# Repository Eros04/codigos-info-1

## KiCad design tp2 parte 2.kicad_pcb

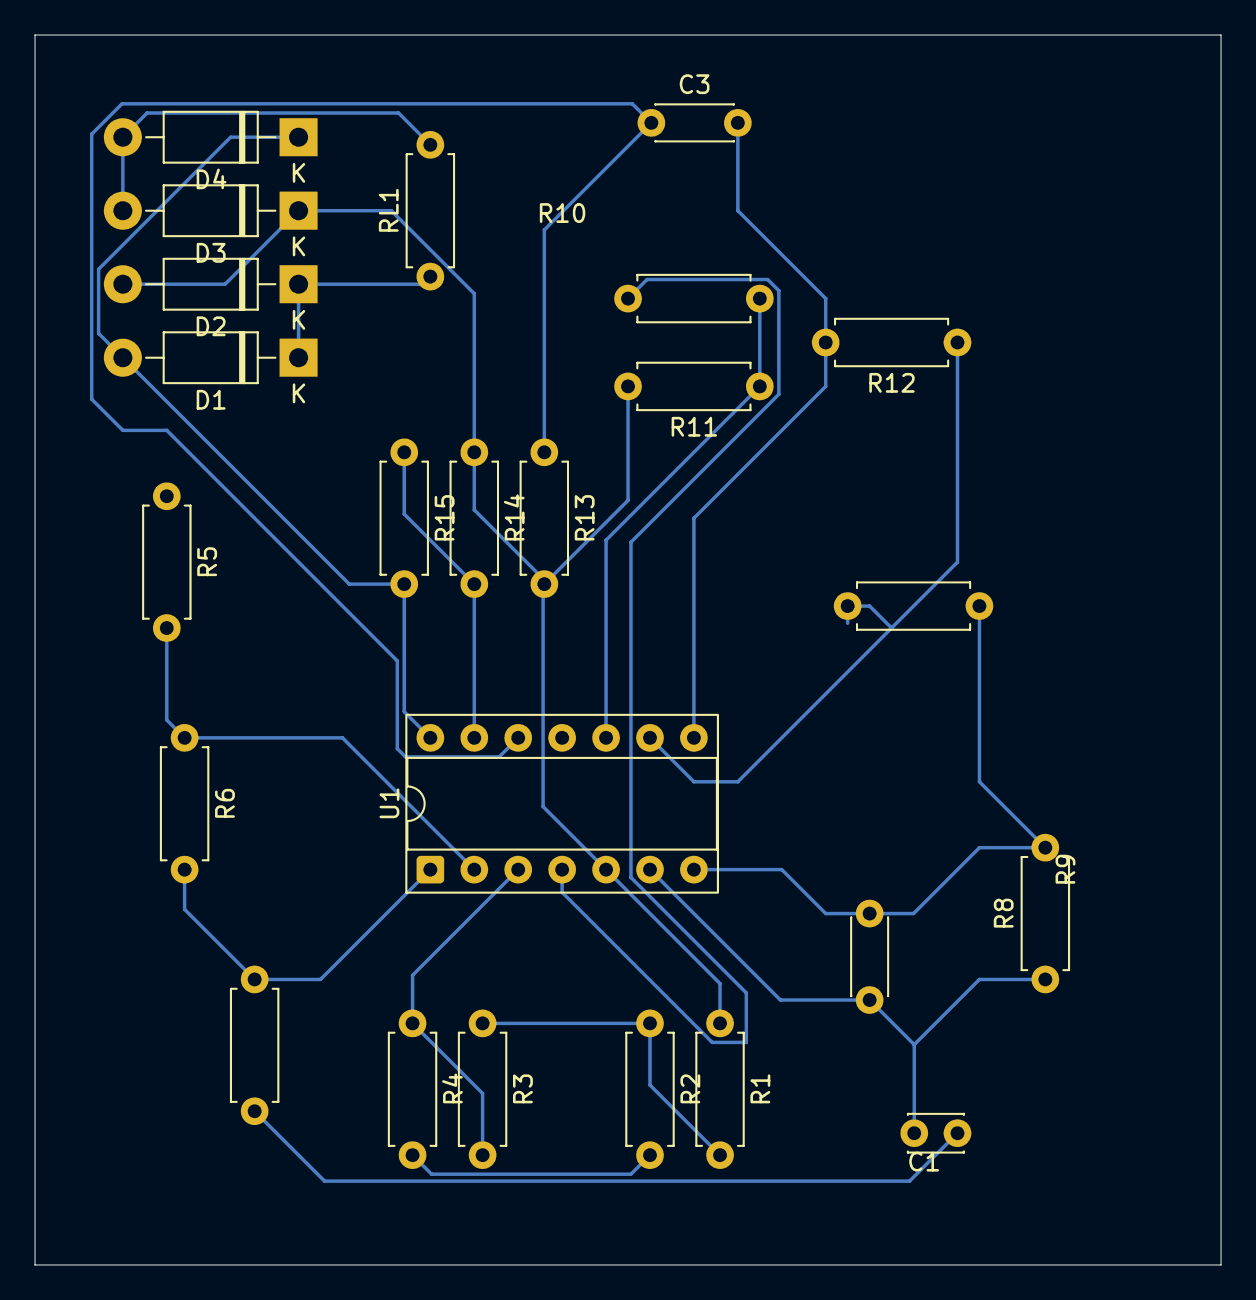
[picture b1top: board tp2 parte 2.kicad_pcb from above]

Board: 2 copper layers, 68.6 x 71.1 mm, 24 parts (0 on the bottom side), 18 nets.

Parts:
C1: 1n; C_Disc_D3.0mm_W2.0mm_P2.50mm
C2: 56p; C_Disc_D4.3mm_W1.9mm_P5.00mm
C3: 10n; C_Disc_D4.3mm_W1.9mm_P5.00mm
D1, D2, D3, D4: 1N5819; D_DO-41_SOD81_P10.16mm_Horizontal
R1: 450; R_Axial_DIN0207_L6.3mm_D2.5mm_P7.62mm_Horizontal
R2: 500; R_Axial_DIN0207_L6.3mm_D2.5mm_P7.62mm_Horizontal
R3, R4, R5, R6: 100k; R_Axial_DIN0207_L6.3mm_D2.5mm_P7.62mm_Horizontal
R7: 4k7; R_Axial_DIN0207_L6.3mm_D2.5mm_P7.62mm_Horizontal
R8: 63k; R_Axial_DIN0207_L6.3mm_D2.5mm_P7.62mm_Horizontal
R9: 56k; R_Axial_DIN0207_L6.3mm_D2.5mm_P7.62mm_Horizontal
R10, R14: 10k; R_Axial_DIN0207_L6.3mm_D2.5mm_P7.62mm_Horizontal
R11: 900; R_Axial_DIN0207_L6.3mm_D2.5mm_P7.62mm_Horizontal
R12: 28k; R_Axial_DIN0207_L6.3mm_D2.5mm_P7.62mm_Horizontal
R13: 470; R_Axial_DIN0207_L6.3mm_D2.5mm_P7.62mm_Horizontal
R15: 6k8; R_Axial_DIN0207_L6.3mm_D2.5mm_P7.62mm_Horizontal
RL1: 100; R_Axial_DIN0207_L6.3mm_D2.5mm_P7.62mm_Horizontal
U1: TL084; DIP-14_W7.62mm_Socket

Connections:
+12V: R10.1, U1.4 (V+)
GND: D2.2 (A), D3.1 (K), R1.1, R11.2, R13.2, R14.1, U1.5 (+)
unnamed: C1.1, R7.2
unnamed: C2.2, R8.2, R9.1, U1.7
unnamed: C3.2, R12.2, U1.8
unnamed: D1.2 (A), D4.1 (K), R15.2, U1.14
unnamed: D1.1 (K), D2.1 (K), RL1.1
unnamed: D3.2 (A), D4.2 (A), RL1.2
unnamed: R1.2, R2.1, R3.1
unnamed: R2.2, R4.2
unnamed: R6.2, R7.1, U1.1
unnamed: R3.2, R4.1, U1.3 (+)
unnamed: R5.2, R6.1, U1.2 (-)
unnamed: C1.2, C2.1, R8.1, U1.6 (-)
unnamed: R10.2, R11.1, U1.10 (+)
unnamed: R9.2, R12.1, U1.9 (-)
unnamed: C3.1, R13.1, U1.12 (+)
unnamed: R14.2, R15.1, U1.13 (-)

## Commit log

2025-05-12 Parte 2 de la Placa de Aplicada
    Revisenla porfa
